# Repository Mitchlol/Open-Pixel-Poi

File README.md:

<h1>
Open Pixel Poi

</h1>

<h4>
  <a href="https://openpixelpoi.com/">Store</a>
  ·
  <a href="./Firmware/MANUAL.md">User Guide</a>
  ·
  <a href="./Hardware/3D Printable Body/README.md">3D Models</a>
  ·
  <a href="./Hardware/Assembly/README.md">Assembly</a>
  ·
  <a href="./Software/README.md">Mobile App</a>
  ·
  <a href="https://mitchlol.github.io/#openpixelpoi">Firmware Tool</a>
  ·
  <a href="https://discord.gg/WpPJEskEuM">Discord</a>
  ·
  <a href="https://www.instagram.com/openpixelpoi">Instagram</a>
</h4>

Open Pixel Poi  is an open source, 3D printable, LED pixel Poi, based around ESP32, WS2812B, and FFF/FDM manufacturing.
Designed to be simple, afforable, repairable, and customizable.
<div>

</div>

#### License
[Licensed  with GPLv3](https://www.gnu.org/licenses/gpl-3.0.en.html)
Suggested donation of 5$ per set of Poi built via [paypal](https://www.paypal.com/donate/?business=MTYSHEQVNBVNQ&amount=5&no_recurring=1&item_name=For+Creating+%26+Maintaing+Open+Pixel+Poi&currency_code=USD) when build without purchasing PCBs from our <a href="https://openpixelpoi.com/">Store</a>.

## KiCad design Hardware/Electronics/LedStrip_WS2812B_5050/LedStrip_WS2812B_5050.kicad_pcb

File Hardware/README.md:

## Lengths:
Tin Strip: 2 * 2"

Switch: 26AAWG 8" Brown & black?

Battery Leads: 20AWG? 5" Red & 1.5" Black

LEDs: 2.5" red/black/white x3

ESP32: 2.25 red/black/white/brown

BMS: 2.25 red/black, 1.5 brown

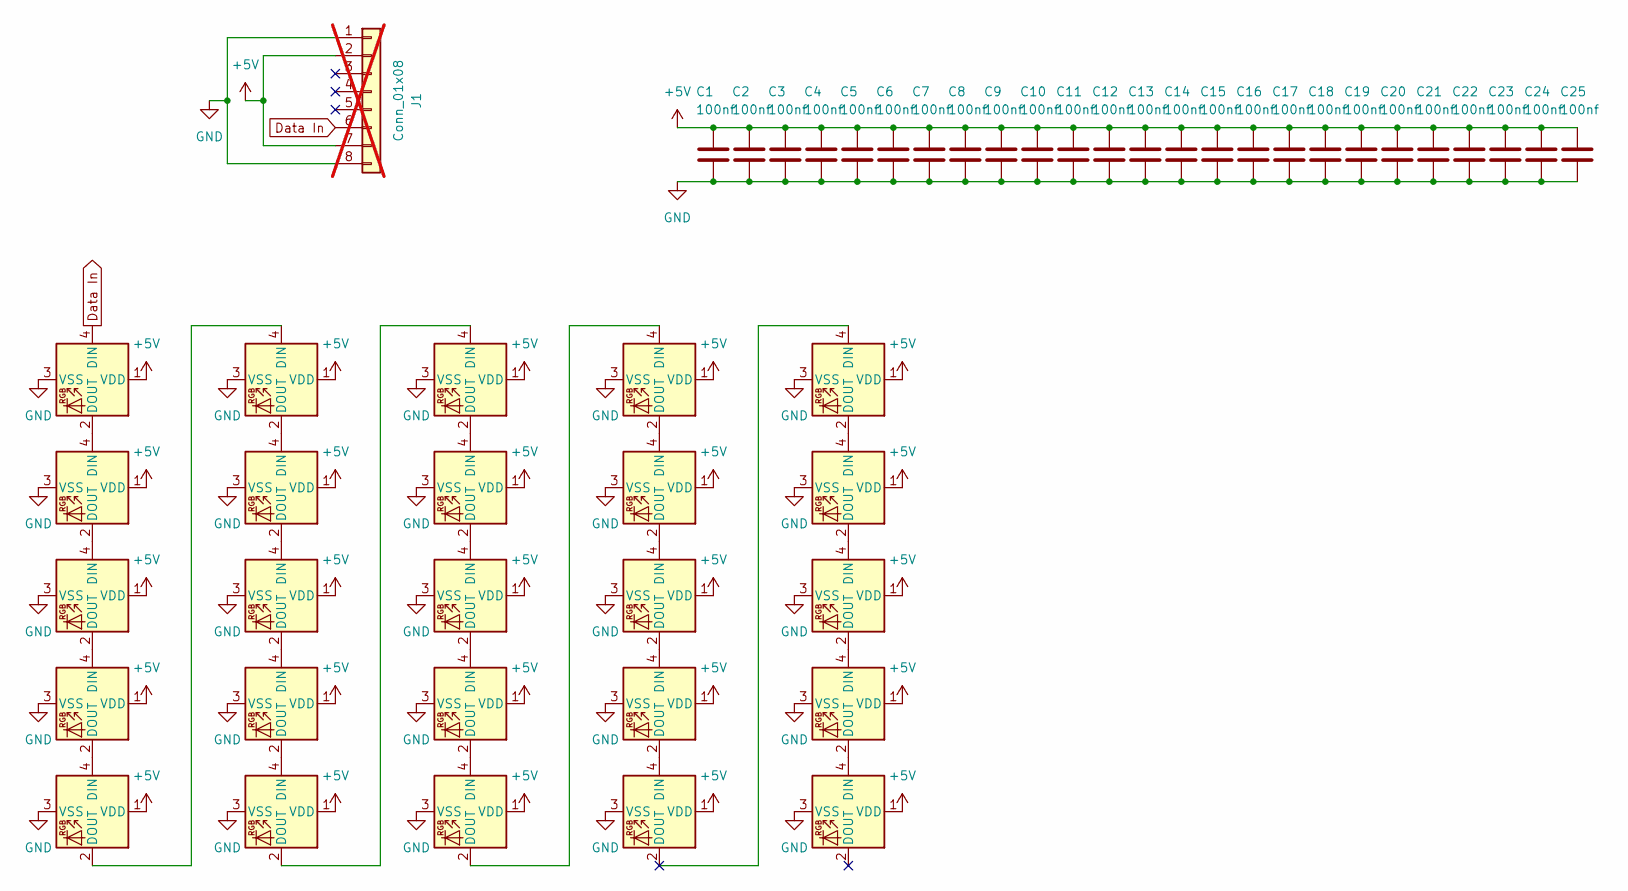
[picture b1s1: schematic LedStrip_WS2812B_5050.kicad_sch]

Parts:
C1, C2, C3, C4, C5, C6, C7, C8, C9, C10, C11, C12, C13, C14, C15, C16, C17, C18, C19, C20, C21, C22, C23, C24, C25: 100nf; C_0402_1005Metric; LCSC C1525
D1, D2, D3, D4, D5, D6, D7, D8, D9, D10, D11, D12, D13, D14, D15, D16, D17, D18, D19, D20, D21, D22, D23, D24, D25: WS2812B; LED_WS2812B_PLCC4_5.0x5.0mm_P3.2mm; LCSC C2843785
J1: Conn_01x08; FPC_01x08_conn; not fitted

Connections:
+5V: C1.1, C2.1, C3.1, C4.1, C5.1, C6.1, C7.1, C8.1, C9.1, C10.1, C11.1, C12.1, C13.1, C14.1, C15.1, C16.1, C17.1, C18.1, C19.1, C20.1, C21.1, C22.1, C23.1, C24.1, C25.1, D1.1 (VDD), D2.1 (VDD), D3.1 (VDD), D4.1 (VDD), D5.1 (VDD), D6.1 (VDD), D7.1 (VDD), D8.1 (VDD), D9.1 (VDD), D10.1 (VDD), D11.1 (VDD), D12.1 (VDD), D13.1 (VDD), D14.1 (VDD), D15.1 (VDD), D16.1 (VDD), D17.1 (VDD), D18.1 (VDD), D19.1 (VDD), D20.1 (VDD), D21.1 (VDD), D22.1 (VDD), D23.1 (VDD), D24.1 (VDD), D25.1 (VDD), J1.2, J1.7
Data In: D1.4 (DIN), J1.6
GND: C1.2, C2.2, C3.2, C4.2, C5.2, C6.2, C7.2, C8.2, C9.2, C10.2, C11.2, C12.2, C13.2, C14.2, C15.2, C16.2, C17.2, C18.2, C19.2, C20.2, C21.2, C22.2, C23.2, C24.2, C25.2, D1.3 (VSS), D2.3 (VSS), D3.3 (VSS), D4.3 (VSS), D5.3 (VSS), D6.3 (VSS), D7.3 (VSS), D8.3 (VSS), D9.3 (VSS), D10.3 (VSS), D11.3 (VSS), D12.3 (VSS), D13.3 (VSS), D14.3 (VSS), D15.3 (VSS), D16.3 (VSS), D17.3 (VSS), D18.3 (VSS), D19.3 (VSS), D20.3 (VSS), D21.3 (VSS), D22.3 (VSS), D23.3 (VSS), D24.3 (VSS), D25.3 (VSS), J1.1, J1.8
unnamed: D1.2 (DOUT), D2.4 (DIN)
unnamed: D2.2 (DOUT), D3.4 (DIN)
unnamed: D3.2 (DOUT), D4.4 (DIN)
unnamed: D4.2 (DOUT), D5.4 (DIN)
unnamed: D5.2 (DOUT), D6.4 (DIN)
unnamed: D6.2 (DOUT), D7.4 (DIN)
unnamed: D7.2 (DOUT), D8.4 (DIN)
unnamed: D8.2 (DOUT), D9.4 (DIN)
unnamed: D9.2 (DOUT), D10.4 (DIN)
unnamed: D10.2 (DOUT), D11.4 (DIN)
unnamed: D11.2 (DOUT), D12.4 (DIN)
unnamed: D12.2 (DOUT), D13.4 (DIN)
unnamed: D13.2 (DOUT), D14.4 (DIN)
unnamed: D14.2 (DOUT), D15.4 (DIN)
unnamed: D15.2 (DOUT), D16.4 (DIN)
unnamed: D16.2 (DOUT), D17.4 (DIN)
unnamed: D17.2 (DOUT), D18.4 (DIN)
unnamed: D18.2 (DOUT), D19.4 (DIN)
unnamed: D19.2 (DOUT), D20.4 (DIN)
unnamed: D21.2 (DOUT), D22.4 (DIN)
unnamed: D22.2 (DOUT), D23.4 (DIN)
unnamed: D23.2 (DOUT), D24.4 (DIN)
unnamed: D24.2 (DOUT), D25.4 (DIN)

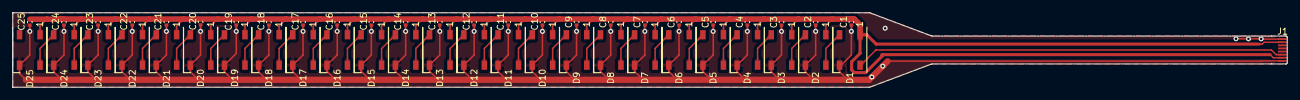
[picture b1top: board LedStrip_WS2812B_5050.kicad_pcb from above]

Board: 2 copper layers, 205.2 x 12.0 mm, 51 parts (0 on the bottom side), 26 nets.

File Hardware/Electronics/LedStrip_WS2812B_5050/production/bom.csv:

Designator,Footprint,Quantity,Value,LCSC Part #
"C1, C10, C11, C12, C13, C14, C15, C16, C17, C18, C19, C2, C20, C3, C4, C5, C6, C7, C8, C9",0402,20,100nf,C1525
"D1, D10, D11, D12, D13, D14, D15, D16, D17, D18, D19, D2, D20, D3, D4, D5, D6, D7, D8, D9",LED_WS2812B_PLCC4_5.0x5.0mm_P3.2mm,20,WS2812B,C2761795

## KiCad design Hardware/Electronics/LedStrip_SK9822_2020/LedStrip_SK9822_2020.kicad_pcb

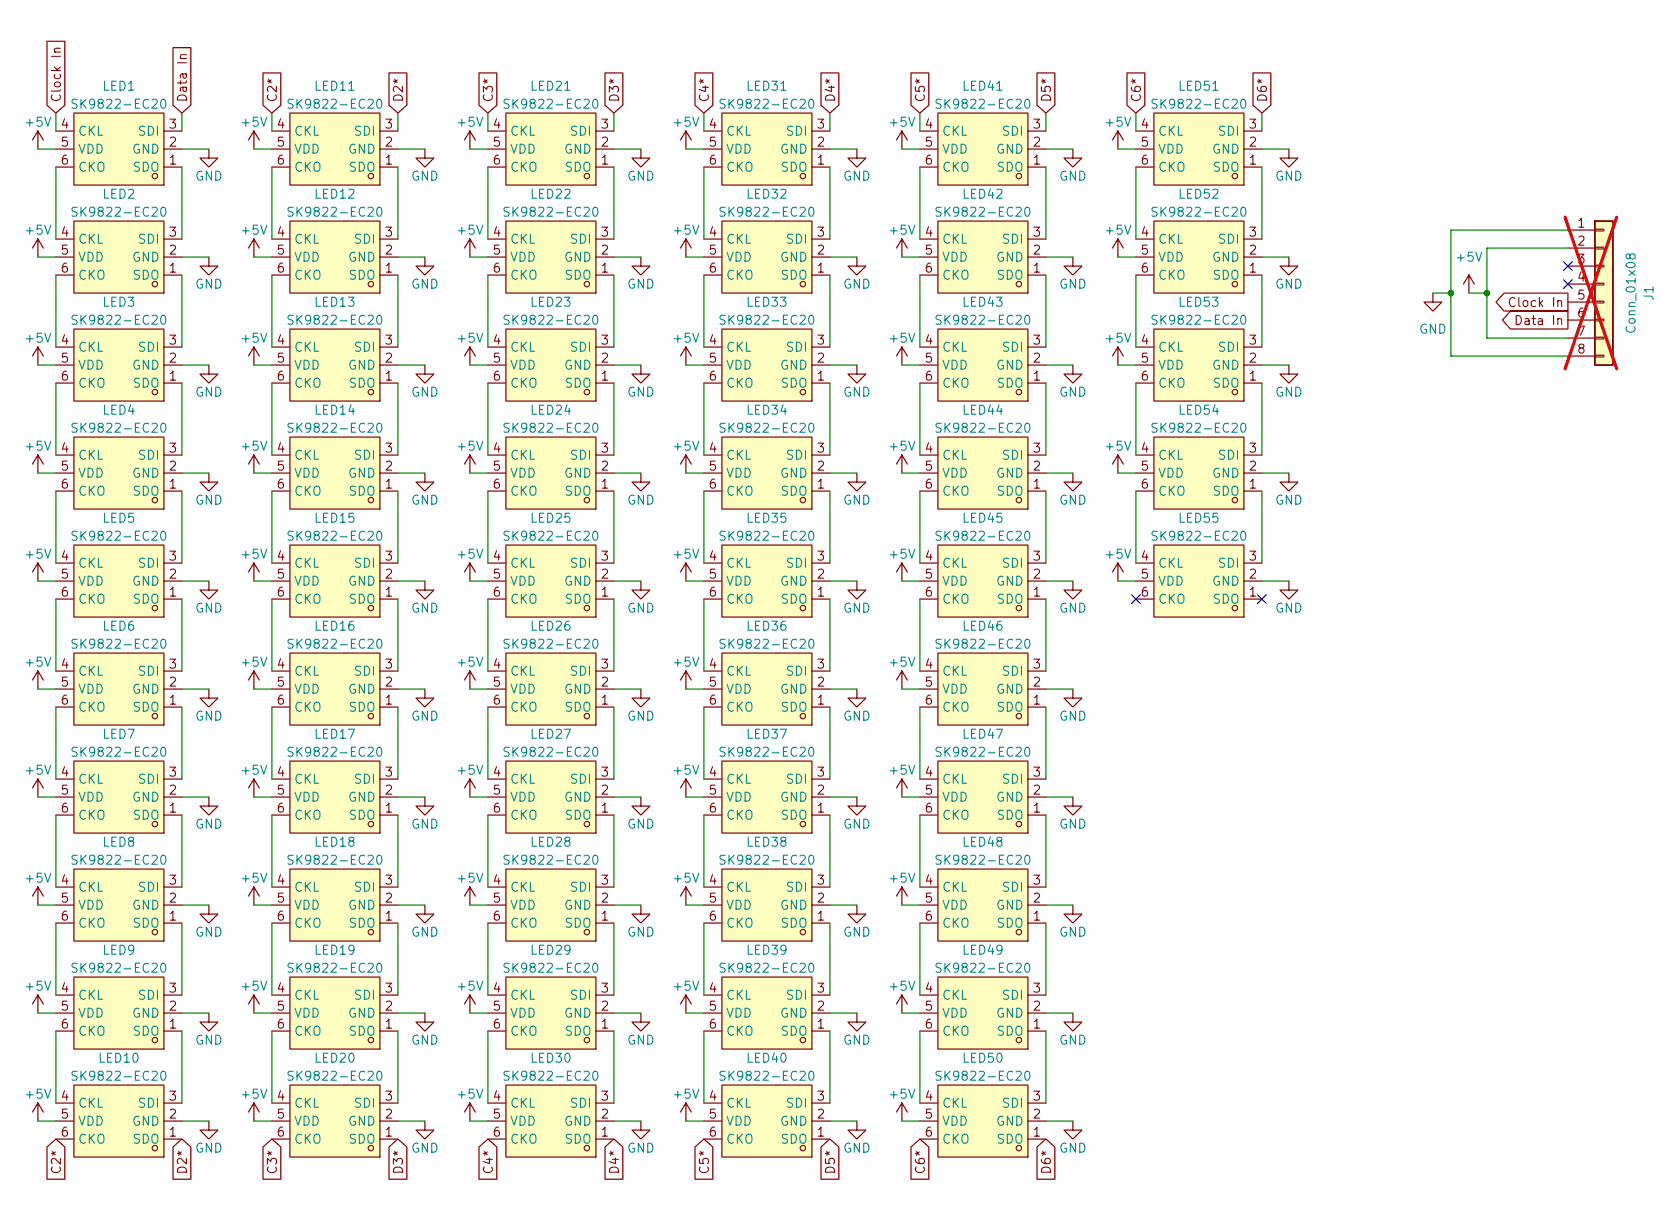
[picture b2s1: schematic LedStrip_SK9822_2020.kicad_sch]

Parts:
J1: Conn_01x08; FPC_01x08_conn; not fitted
LED1, LED2, LED3, LED4, LED5, LED6, LED7, LED8, LED9, LED10, LED11, LED12, LED13, LED14, LED15, LED16, LED17, LED18, LED19, LED20, LED21, LED22, LED23, LED24, LED25, LED26, LED27, LED28, LED29, LED30, LED31, LED32, LED33, LED34, LED35, LED36, LED37, LED38, LED39, LED40, LED41, LED42, LED43, LED44, LED45, LED46, LED47, LED48, LED49, LED50, LED51, LED52, LED53, LED54, LED55: SK9822-EC20; LED-SMD_6P-L2.0-W2.0-P0.80-TL; LCSC Part C2909059

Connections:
+5V: J1.2, J1.7, LED1.5 (VDD), LED2.5 (VDD), LED3.5 (VDD), LED4.5 (VDD), LED5.5 (VDD), LED6.5 (VDD), LED7.5 (VDD), LED8.5 (VDD), LED9.5 (VDD), LED10.5 (VDD), LED11.5 (VDD), LED12.5 (VDD), LED13.5 (VDD), LED14.5 (VDD), LED15.5 (VDD), LED16.5 (VDD), LED17.5 (VDD), LED18.5 (VDD), LED19.5 (VDD), LED20.5 (VDD), LED21.5 (VDD), LED22.5 (VDD), LED23.5 (VDD), LED24.5 (VDD), LED25.5 (VDD), LED26.5 (VDD), LED27.5 (VDD), LED28.5 (VDD), LED29.5 (VDD), LED30.5 (VDD), LED31.5 (VDD), LED32.5 (VDD), LED33.5 (VDD), LED34.5 (VDD), LED35.5 (VDD), LED36.5 (VDD), LED37.5 (VDD), LED38.5 (VDD), LED39.5 (VDD), LED40.5 (VDD), LED41.5 (VDD), LED42.5 (VDD), LED43.5 (VDD), LED44.5 (VDD), LED45.5 (VDD), LED46.5 (VDD), LED47.5 (VDD), LED48.5 (VDD), LED49.5 (VDD), LED50.5 (VDD), LED51.5 (VDD), LED52.5 (VDD), LED53.5 (VDD), LED54.5 (VDD), LED55.5 (VDD)
C2*: LED10.6 (CKO), LED11.4 (CKL)
C3*: LED20.6 (CKO), LED21.4 (CKL)
C4*: LED30.6 (CKO), LED31.4 (CKL)
C5*: LED40.6 (CKO), LED41.4 (CKL)
C6*: LED50.6 (CKO), LED51.4 (CKL)
Clock In: J1.5, LED1.4 (CKL)
D2*: LED10.1 (SDO), LED11.3 (SDI)
D3*: LED20.1 (SDO), LED21.3 (SDI)
D4*: LED30.1 (SDO), LED31.3 (SDI)
D5*: LED40.1 (SDO), LED41.3 (SDI)
D6*: LED50.1 (SDO), LED51.3 (SDI)
Data In: J1.6, LED1.3 (SDI)
GND: J1.1, J1.8, LED1.2 (GND), LED2.2 (GND), LED3.2 (GND), LED4.2 (GND), LED5.2 (GND), LED6.2 (GND), LED7.2 (GND), LED8.2 (GND), LED9.2 (GND), LED10.2 (GND), LED11.2 (GND), LED12.2 (GND), LED13.2 (GND), LED14.2 (GND), LED15.2 (GND), LED16.2 (GND), LED17.2 (GND), LED18.2 (GND), LED19.2 (GND), LED20.2 (GND), LED21.2 (GND), LED22.2 (GND), LED23.2 (GND), LED24.2 (GND), LED25.2 (GND), LED26.2 (GND), LED27.2 (GND), LED28.2 (GND), LED29.2 (GND), LED30.2 (GND), LED31.2 (GND), LED32.2 (GND), LED33.2 (GND), LED34.2 (GND), LED35.2 (GND), LED36.2 (GND), LED37.2 (GND), LED38.2 (GND), LED39.2 (GND), LED40.2 (GND), LED41.2 (GND), LED42.2 (GND), LED43.2 (GND), LED44.2 (GND), LED45.2 (GND), LED46.2 (GND), LED47.2 (GND), LED48.2 (GND), LED49.2 (GND), LED50.2 (GND), LED51.2 (GND), LED52.2 (GND), LED53.2 (GND), LED54.2 (GND), LED55.2 (GND)
unnamed: LED1.6 (CKO), LED2.4 (CKL)
unnamed: LED1.1 (SDO), LED2.3 (SDI)
unnamed: LED2.6 (CKO), LED3.4 (CKL)
unnamed: LED2.1 (SDO), LED3.3 (SDI)
unnamed: LED3.6 (CKO), LED4.4 (CKL)
unnamed: LED3.1 (SDO), LED4.3 (SDI)
unnamed: LED4.6 (CKO), LED5.4 (CKL)
unnamed: LED4.1 (SDO), LED5.3 (SDI)
unnamed: LED5.6 (CKO), LED6.4 (CKL)
unnamed: LED5.1 (SDO), LED6.3 (SDI)
unnamed: LED6.6 (CKO), LED7.4 (CKL)
unnamed: LED6.1 (SDO), LED7.3 (SDI)
unnamed: LED7.6 (CKO), LED8.4 (CKL)
unnamed: LED7.1 (SDO), LED8.3 (SDI)
unnamed: LED8.6 (CKO), LED9.4 (CKL)
unnamed: LED8.1 (SDO), LED9.3 (SDI)
unnamed: LED9.6 (CKO), LED10.4 (CKL)
unnamed: LED9.1 (SDO), LED10.3 (SDI)
unnamed: LED11.6 (CKO), LED12.4 (CKL)
unnamed: LED11.1 (SDO), LED12.3 (SDI)
unnamed: LED12.6 (CKO), LED13.4 (CKL)
unnamed: LED12.1 (SDO), LED13.3 (SDI)
unnamed: LED13.6 (CKO), LED14.4 (CKL)
unnamed: LED13.1 (SDO), LED14.3 (SDI)
unnamed: LED14.6 (CKO), LED15.4 (CKL)
unnamed: LED14.1 (SDO), LED15.3 (SDI)
unnamed: LED15.6 (CKO), LED16.4 (CKL)
unnamed: LED15.1 (SDO), LED16.3 (SDI)
unnamed: LED16.6 (CKO), LED17.4 (CKL)
unnamed: LED16.1 (SDO), LED17.3 (SDI)
unnamed: LED17.6 (CKO), LED18.4 (CKL)
unnamed: LED17.1 (SDO), LED18.3 (SDI)
unnamed: LED18.6 (CKO), LED19.4 (CKL)
unnamed: LED18.1 (SDO), LED19.3 (SDI)
unnamed: LED19.6 (CKO), LED20.4 (CKL)
unnamed: LED19.1 (SDO), LED20.3 (SDI)
unnamed: LED21.6 (CKO), LED22.4 (CKL)
unnamed: LED21.1 (SDO), LED22.3 (SDI)
unnamed: LED22.6 (CKO), LED23.4 (CKL)
unnamed: LED22.1 (SDO), LED23.3 (SDI)
unnamed: LED23.6 (CKO), LED24.4 (CKL)
unnamed: LED23.1 (SDO), LED24.3 (SDI)
unnamed: LED24.6 (CKO), LED25.4 (CKL)
unnamed: LED24.1 (SDO), LED25.3 (SDI)
unnamed: LED25.6 (CKO), LED26.4 (CKL)
unnamed: LED25.1 (SDO), LED26.3 (SDI)
unnamed: LED26.6 (CKO), LED27.4 (CKL)
unnamed: LED26.1 (SDO), LED27.3 (SDI)
unnamed: LED27.6 (CKO), LED28.4 (CKL)
unnamed: LED27.1 (SDO), LED28.3 (SDI)
unnamed: LED28.6 (CKO), LED29.4 (CKL)
unnamed: LED28.1 (SDO), LED29.3 (SDI)
unnamed: LED29.6 (CKO), LED30.4 (CKL)
unnamed: LED29.1 (SDO), LED30.3 (SDI)
unnamed: LED31.6 (CKO), LED32.4 (CKL)
unnamed: LED31.1 (SDO), LED32.3 (SDI)
unnamed: LED32.6 (CKO), LED33.4 (CKL)
unnamed: LED32.1 (SDO), LED33.3 (SDI)
unnamed: LED33.6 (CKO), LED34.4 (CKL)
unnamed: LED33.1 (SDO), LED34.3 (SDI)
unnamed: LED34.6 (CKO), LED35.4 (CKL)
unnamed: LED34.1 (SDO), LED35.3 (SDI)
unnamed: LED35.6 (CKO), LED36.4 (CKL)
unnamed: LED35.1 (SDO), LED36.3 (SDI)
unnamed: LED36.6 (CKO), LED37.4 (CKL)
unnamed: LED36.1 (SDO), LED37.3 (SDI)
unnamed: LED37.6 (CKO), LED38.4 (CKL)
unnamed: LED37.1 (SDO), LED38.3 (SDI)
unnamed: LED38.6 (CKO), LED39.4 (CKL)
unnamed: LED38.1 (SDO), LED39.3 (SDI)
unnamed: LED39.6 (CKO), LED40.4 (CKL)
unnamed: LED39.1 (SDO), LED40.3 (SDI)
unnamed: LED41.6 (CKO), LED42.4 (CKL)
unnamed: LED41.1 (SDO), LED42.3 (SDI)
unnamed: LED42.6 (CKO), LED43.4 (CKL)
unnamed: LED42.1 (SDO), LED43.3 (SDI)
unnamed: LED43.6 (CKO), LED44.4 (CKL)
unnamed: LED43.1 (SDO), LED44.3 (SDI)
unnamed: LED44.6 (CKO), LED45.4 (CKL)
unnamed: LED44.1 (SDO), LED45.3 (SDI)
unnamed: LED45.6 (CKO), LED46.4 (CKL)
unnamed: LED45.1 (SDO), LED46.3 (SDI)
unnamed: LED46.6 (CKO), LED47.4 (CKL)
unnamed: LED46.1 (SDO), LED47.3 (SDI)
unnamed: LED47.6 (CKO), LED48.4 (CKL)
unnamed: LED47.1 (SDO), LED48.3 (SDI)
unnamed: LED48.6 (CKO), LED49.4 (CKL)
unnamed: LED48.1 (SDO), LED49.3 (SDI)
unnamed: LED49.6 (CKO), LED50.4 (CKL)
unnamed: LED49.1 (SDO), LED50.3 (SDI)
unnamed: LED51.6 (CKO), LED52.4 (CKL)
unnamed: LED51.1 (SDO), LED52.3 (SDI)
unnamed: LED52.6 (CKO), LED53.4 (CKL)
unnamed: LED52.1 (SDO), LED53.3 (SDI)
unnamed: LED53.6 (CKO), LED54.4 (CKL)
unnamed: LED53.1 (SDO), LED54.3 (SDI)
unnamed: LED54.6 (CKO), LED55.4 (CKL)
unnamed: LED54.1 (SDO), LED55.3 (SDI)

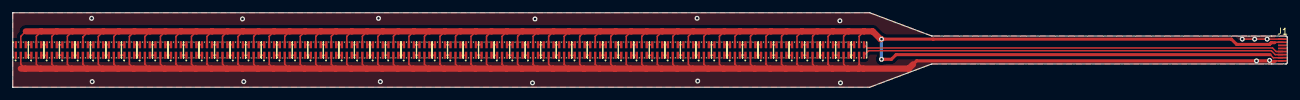
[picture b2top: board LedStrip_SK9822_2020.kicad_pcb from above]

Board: 2 copper layers, 205.2 x 12.0 mm, 56 parts (0 on the bottom side), 112 nets.

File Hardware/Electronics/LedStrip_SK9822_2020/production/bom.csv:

Designator,Footprint,Quantity,Value,LCSC Part #
"LED1, LED10, LED11, LED12, LED13, LED14, LED15, LED16, LED17, LED18, LED19, LED2, LED20, LED21, LED22, LED23, LED24, LED25, LED26, LED27, LED28, LED29, LED3, LED30, LED31, LED32, LED33, LED34, LED35, LED36, LED37, LED38, LED39, LED4, LED40, LED41, LED42, LED43, LED44, LED45, LED46, LED47, LED48, LED49, LED5, LED50, LED51, LED52, LED53, LED54, LED55, LED6, LED7, LED8, LED9",LED-SMD_6P-L2.0-W2.0-P0.80-TL,55,SK9822-EC20,C2909059

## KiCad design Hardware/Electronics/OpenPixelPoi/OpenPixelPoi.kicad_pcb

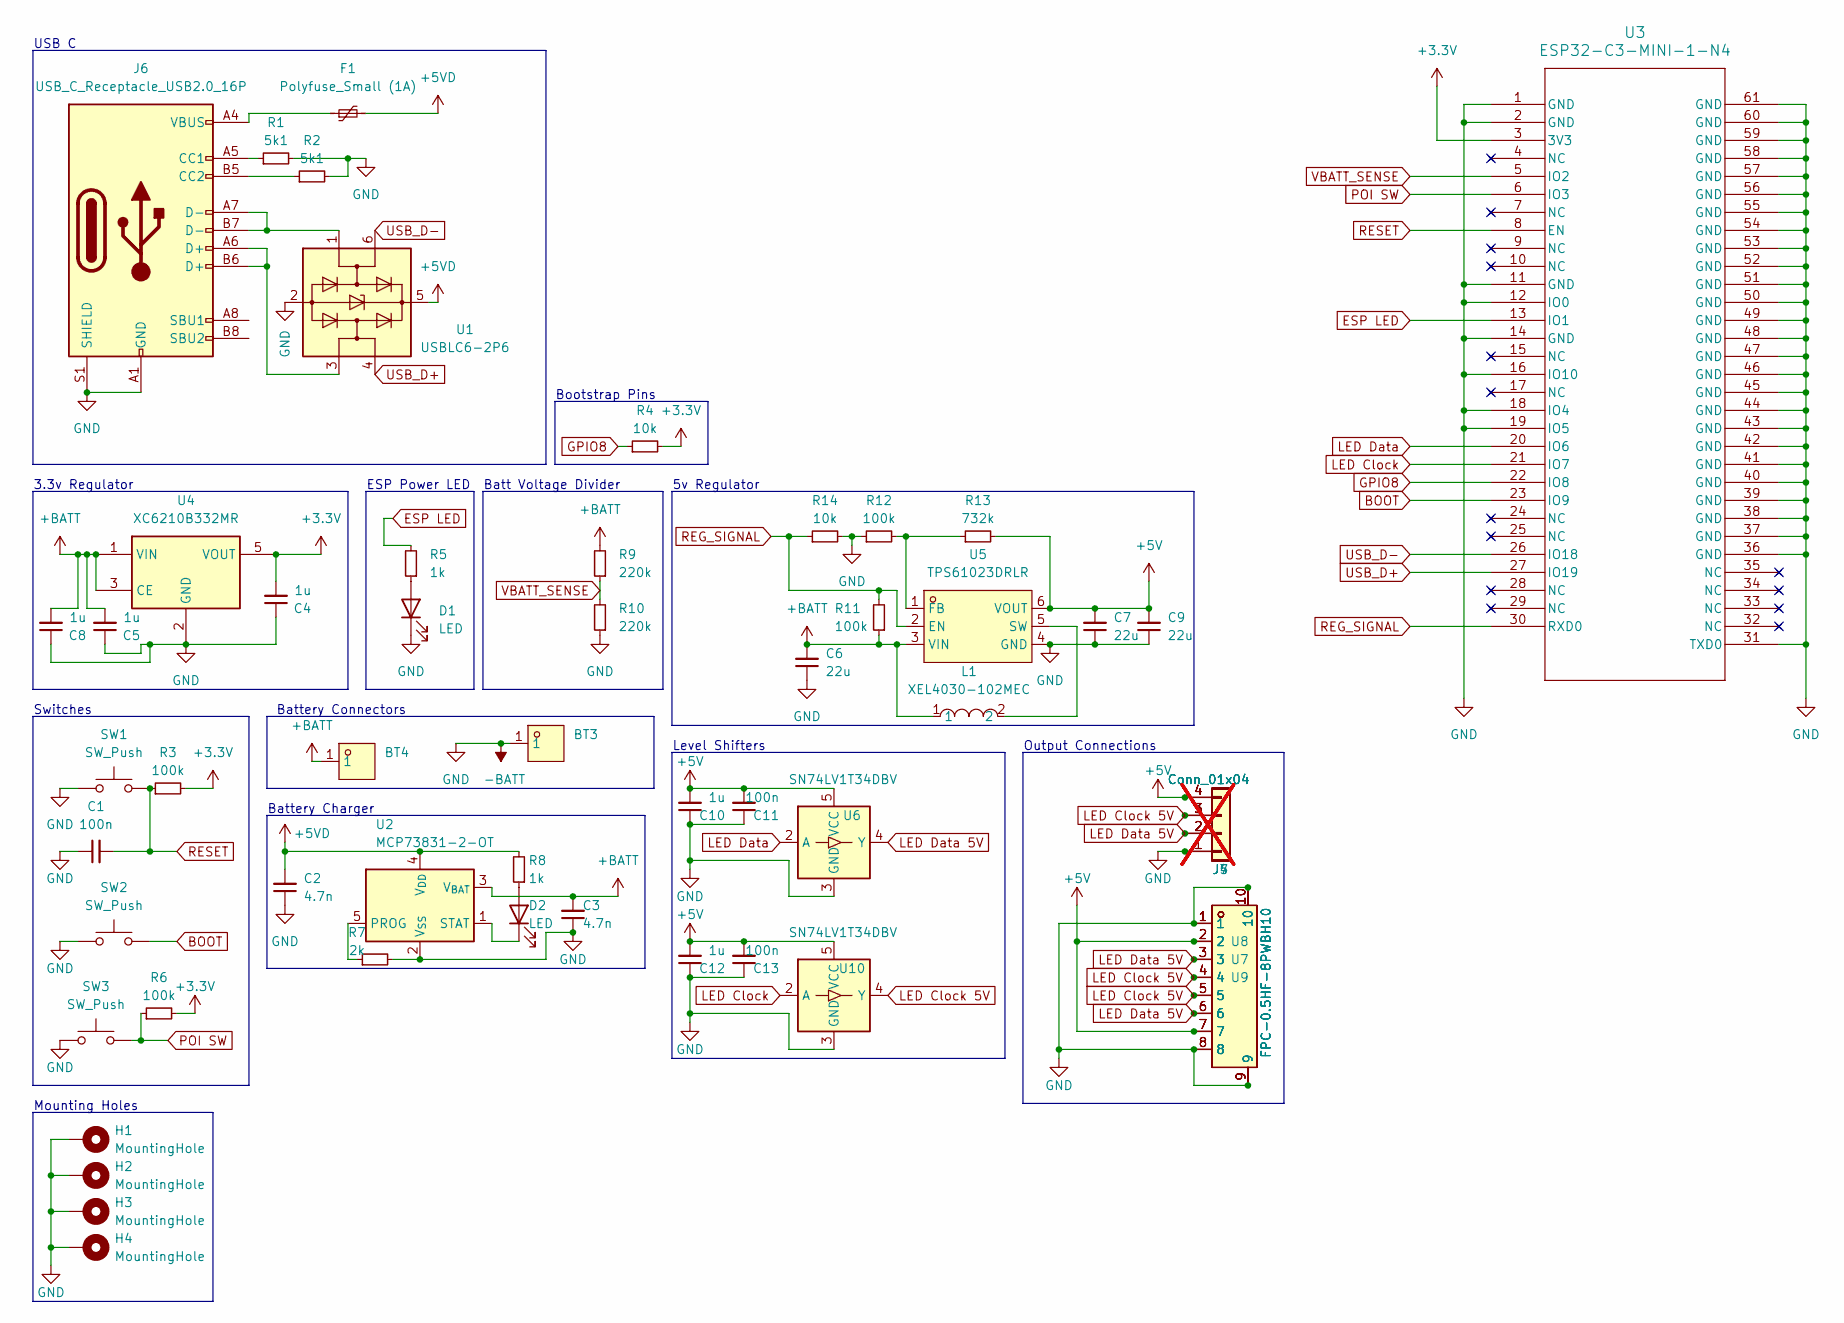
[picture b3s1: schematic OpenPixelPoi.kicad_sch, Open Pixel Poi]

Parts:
BT3, BT4: MY-ZJ-110; SMD_MY-ZJ-110; LCSC Part C964859
C1, C11, C13: 100n; C_0805_2012Metric; LCSC C83055
C2, C3: 4.7n; C_0805_2012Metric; LCSC C123621
C4, C5, C8, C10, C12: 1u; C_0805_2012Metric; LCSC C28323
C6, C7, C9: 22u; C_0805_2012Metric; LCSC C45783
D1, D2: LED; LED_0603_1608Metric; LCSC C965807
F1: Polyfuse_Small (1A); Fuse_1206_3216Metric; LCSC C720075
H1, H2, H3, H4: MountingHole; MountingHole_3.2mm_M3_Pad
J4, J5, J7: Conn_01x04; PinHeader_1x04_P2.00mm_Vertical; not fitted
J6: USB_C_Receptacle_USB2.0_16P; USB_C_Receptacle_HRO_TYPE-C-31-M-12; LCSC C2765186
L1: XEL4030-102MEC; IND-SMD_L4.0-W4.0-A; LCSC Part C5441341
R1, R2: 5k1; R_0603_1608Metric; LCSC C14677
R3, R6, R11, R12: 100k; R_0603_1608Metric; LCSC C14675
R4, R14: 10k; R_0603_1608Metric; LCSC C98220
R5, R8: 1k; R_0603_1608Metric; LCSC C22548
R7: 2k; R_0603_1608Metric; LCSC C22975
R9, R10: 220k; R_0603_1608Metric; LCSC C22961
R13: 732k; R_0603_1608Metric; LCSC C246003
SW1, SW2: SW_Push; SW_SPST_B3U-1000P; LCSC C19270949
SW3: SW_Push; Panasonic_EVQPUL_EVQPUC; LCSC C397351
U1: USBLC6-2P6; SOT-666; LCSC C15999
U2: MCP73831-2-OT; SOT-23-5; LCSC C424093
U3: ESP32-C3-MINI-1-N4; ESP32-C3-MINI-1_EXP; LCSC C2934569
U4: XC6210B332MR; SOT-23-5; LCSC C47719
U5: TPS61023DRLR; SOT-563_L1.6-W1.2-P0.50-LS1.6-BR; LCSC Part C919459
U6, U10: SN74LV1T34DBV; SOT-23-5; LCSC C100024
U7, U8, U9: FPC-0.5HF-8PWBH10; FPC-SMD_8P-P0.50_XUNPU_FPC-0.5HF-8PWBH10; LCSC Part C5343275

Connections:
+3.3V: C4.2, R3.2, R4.2, R6.2, U3.3 (3V3), U4.5 (VOUT)
+5V: C7.2, C9.2, C10.2, C11.2, C12.2, C13.2, J4.4, J5.4, J7.4, R13.2, U5.6 (VOUT), U6.5 (VCC), U7.2, U7.7, U8.2, U8.7, U9.2, U9.7, U10.5 (VCC)
+5VD: C2.2, F1.2, R8.2, U1.5 (VBUS), U2.4 (V_{DD})
+BATT: BT4.1, C3.2, C5.2, C6.2, C8.2, L1.1, R9.2, R11.1, U2.3 (V_{BAT}), U4.1 (VIN), U4.3 (CE), U5.3 (VIN)
-BATT: BT3.1, C1.1, C2.1, C3.1, C4.1, C5.1, C6.1, C7.1, C8.1, C9.1, C10.1, C11.1, C12.1, C13.1, D1.1 (K), H1.1, H2.1, H3.1, H4.1, J4.1, J5.1, J6.A1 (GND), J6.A12 (GND), J6.B1 (GND), J6.B12 (GND), J6.S1 (SHIELD), J7.1, R1.2, R2.2, R7.2, R10.1, R12.1, R14.2, SW1.1, SW2.1, SW3.1, U1.2 (GND), U2.2 (V_{SS}), U3.1 (GND), U3.2 (GND), U3.11 (GND), U3.12 (IO0), U3.14 (GND), U3.16 (IO10), U3.18 (IO4), U3.19 (IO5), U3.31 (TXD0), U3.36 (GND), U3.37 (GND), U3.38 (GND), U3.39 (GND), U3.40 (GND), U3.41 (GND), U3.42 (GND), U3.43 (GND), U3.44 (GND), U3.45 (GND), U3.46 (GND), U3.47 (GND), U3.48 (GND), U3.49 (GND), U3.50 (GND), U3.51 (GND), U3.52 (GND), U3.53 (GND), U3.54 (GND), U3.55 (GND), U3.56 (GND), U3.57 (GND), U3.58 (GND), U3.59 (GND), U3.60 (GND), U3.61 (GND), U4.2 (GND), U5.4 (GND), U6.3 (GND), U7.1, U7.8, U7.9, U7.10, U8.1, U8.8, U8.9, U8.10, U9.1, U9.8, U9.9, U9.10, U10.3 (GND)
BOOT: SW2.2, U3.23 (IO9)
ESP LED: R5.2, U3.13 (IO1)
GPIO8: R4.1, U3.22 (IO8)
LED Clock: U3.21 (IO7), U10.2 (A)
LED Clock 5V: J4.3, J5.3, J7.3, U7.4, U7.5, U8.4, U8.5, U9.4, U9.5, U10.4 (Y)
LED Data: U3.20 (IO6), U6.2 (A)
LED Data 5V: J4.2, J5.2, J7.2, U6.4 (Y), U7.3, U7.6, U8.3, U8.6, U9.3, U9.6
unnamed: D1.2 (A), R5.1
unnamed: D2.2 (A), R8.1
unnamed: D2.1 (K), U2.1 (STAT)
unnamed: F1.1, J6.A4 (VBUS), J6.A9 (VBUS), J6.B4 (VBUS), J6.B9 (VBUS)
unnamed: J6.A5 (CC1), R1.1
unnamed: J6.B5 (CC2), R2.1
unnamed: J6.A6 (D+), J6.B6 (D+), U1.3 (I/O2)
unnamed: J6.A7 (D-), J6.B7 (D-), U1.1 (I/O1)
unnamed: R7.1, U2.5 (PROG)
unnamed: R12.2, R13.1, U5.1 (FB)
unnamed: L1.2, U5.5 (SW)
POI SW: R6.1, SW3.2, U3.6 (IO3)
REG_SIGNAL: R11.2, R14.1, U3.30 (RXD0), U5.2 (EN)
RESET: C1.2, R3.1, SW1.2, U3.8 (EN)
USB_D+: U1.4 (I/O2), U3.27 (IO19)
USB_D-: U1.6 (I/O1), U3.26 (IO18)
VBATT_SENSE: R9.1, R10.2, U3.5 (IO2)

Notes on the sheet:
Battery Connectors
Output Connections
Batt Voltage Divider
Mounting Holes
Level Shifters
USB C
5v Regulator
3.3v Regulator
ESP Power LED
Bootstrap Pins
Switches
Battery Charger

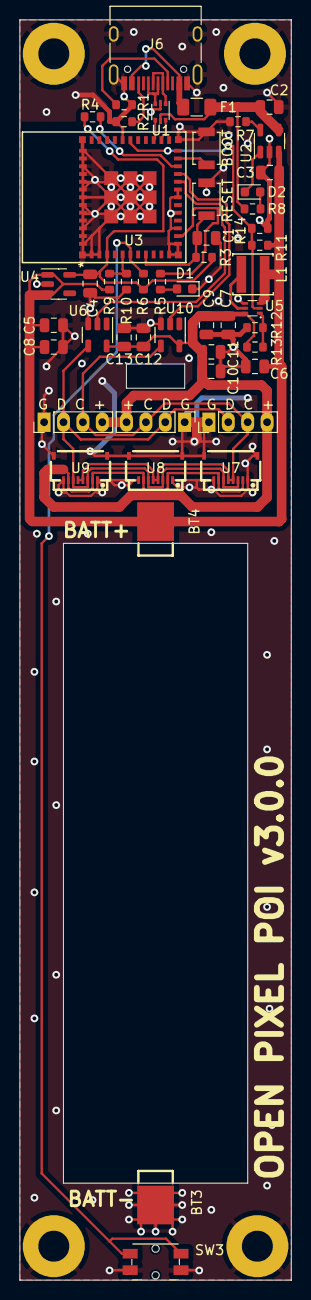
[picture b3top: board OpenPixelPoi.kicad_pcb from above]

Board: 2 copper layers, 28.0 x 130.0 mm, 54 parts (0 on the bottom side), 29 nets.

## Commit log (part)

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2023-05-15 delay => millis() start stubbing in new pattern class
2023-05-21 Working version using patterns; patterns class needs a refactor
2023-05-21 working version of patterns/loadPattern (without using the pattern parameter); remove unused code
2023-05-21 use loadPattern for both patterns; use pattern param in loadPattern
2023-05-21 factor out updatePattern()
2023-05-22 more patterns
2023-05-26 fix merge conflicts
2023-05-27 drop in replace of flutter_blue_plus
2023-05-27 migrate to flutter_blue_plus
2023-05-29 Update comments
2025-05-05 Fix edge to edge
2025-05-05 Get web/windows running, fix empy db on load, add rotate & blur
2025-05-05 Update store link
2025-05-06 Fix readme
2025-05-20 windows & web releases, readme updates
2025-05-20 Readme update
2025-05-21 Knobs and tweaks
2025-06-09 Add more 3d files
2025-06-09 Link to extras
2025-06-09 tweak
2025-06-09 tweak2
2025-06-09 Knew i forgot a con!
2025-06-11 Firmware: min speed is 1fps, new shutdown animation, pattern bank menu redone
2025-06-12 Add soldering video link
2025-08-07 Remove arduino ide, reduce shutdown timer.
2025-11-23 Update reademe to match latest firmware
2025-11-25 Add Clock pinout & FPC connectors to PCB, start on basic ws2812b LED strip.
2025-11-26 Add 20 and 55 pixel strips
2025-11-26 Add pullup to gpio8, change board "version" to 3.0.0 due to new data pinout.
2025-11-26 rename main kicad project
2025-11-26 fix lib model links
2025-11-26 Rename WS2812B project
2025-11-26 Rename SK9822 led strip project
2025-11-26 rerename ws2812 strip
2025-11-26 Add higher density ws2812b strip
2025-11-26 Cleanup
2025-11-27 stuff
2025-11-28 Switch to neopixel bus, add fw version checking, migrate to fw 2, 16bit fps values, change fw to app message format, fix fps bug, add config file, add preliminary support for sk9822/variable led coun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
2025-11-29 Properly configurable led count, type, and hardware version
2025-11-29 Editable ble device names
2025-11-29 Pixel UI updates for variable pixel counts.
2025-11-30 Import and load images of any aspect ratio with a max of 40000 pixels
2025-12-01 Add pattern sequencer
2025-12-16 Use 20Mhz hardware SPI for dotstar
2025-12-17 Add brigtness scaling based on curent consumption
2025-12-20 Fix speed and duration in sequence creator, allow larger check patterns.
2025-12-20 Add hex shell with no diffusion
2025-12-20 Final pcb tweaks before large order
2025-12-20 Fix slight lag every 2 seconds that has been annoying me for years
2025-12-20 Add config templates for common hardware configurations
2025-12-20 Switch spiffs to little FS and load patterns in chunks to reduce large lag spike on pattern change.
2025-12-21 Include default patterns in firmware
2025-12-21 Limit sk9822 to levels that dont cause retinal damage or melt the leds.
2025-12-21 Fix sequencer getting ahead of partially loaded images
2025-12-22 Change brightness and speed to utilize 6 "options" that are modifable. Make "demo" speed adjustable
2025-12-23 Dumb down app's default patterns to tile better for different sizes.
2025-12-23 Upgrade pattern creators to work for larger images
2025-12-24 Tweak defaults
2025-12-24 Sequence ui imporvements
2025-12-24 Clean up config
2025-12-24 Include more shells and update 3d print readme
2025-12-25 Release app 2.0.0
2025-12-26 repair brightness logic
2025-12-27 Readme updates
2025-12-30 Assembly readme improvements
2025-12-30 try H3
2025-12-30 yep, h3
2025-12-30 More readmes
2025-12-30 Add a little more space around button in an attempt to prevent them tearing off during removal
2026-01-01 Clean up shutdown animation
2026-01-01 Update hex cap file to be easier to get on but not off.
2026-01-02 Break led strip code into seperate files
2026-01-02 Add web app 2.0
2026-01-02 Release windows app 2.0.0
2026-01-02 Cleanup readme
2026-01-07 Fix preference keys longer than 15 char limit
2026-01-08 Assembly Guide Imporvements
2026-01-08 Even better assembly guide
2026-01-23 Fix pattern looping desync
2026-02-11 Add Snap Cap Beta files.
2026-02-13 Snap Cap B & some documentation
2026-02-19 Adjust tolerances on snap caps for easier assembly, add 3rd cap with simple hole
2026-02-19 Add chamfer to help lift snaps, update readme.
2026-06-16 Fix link to windows app v2
